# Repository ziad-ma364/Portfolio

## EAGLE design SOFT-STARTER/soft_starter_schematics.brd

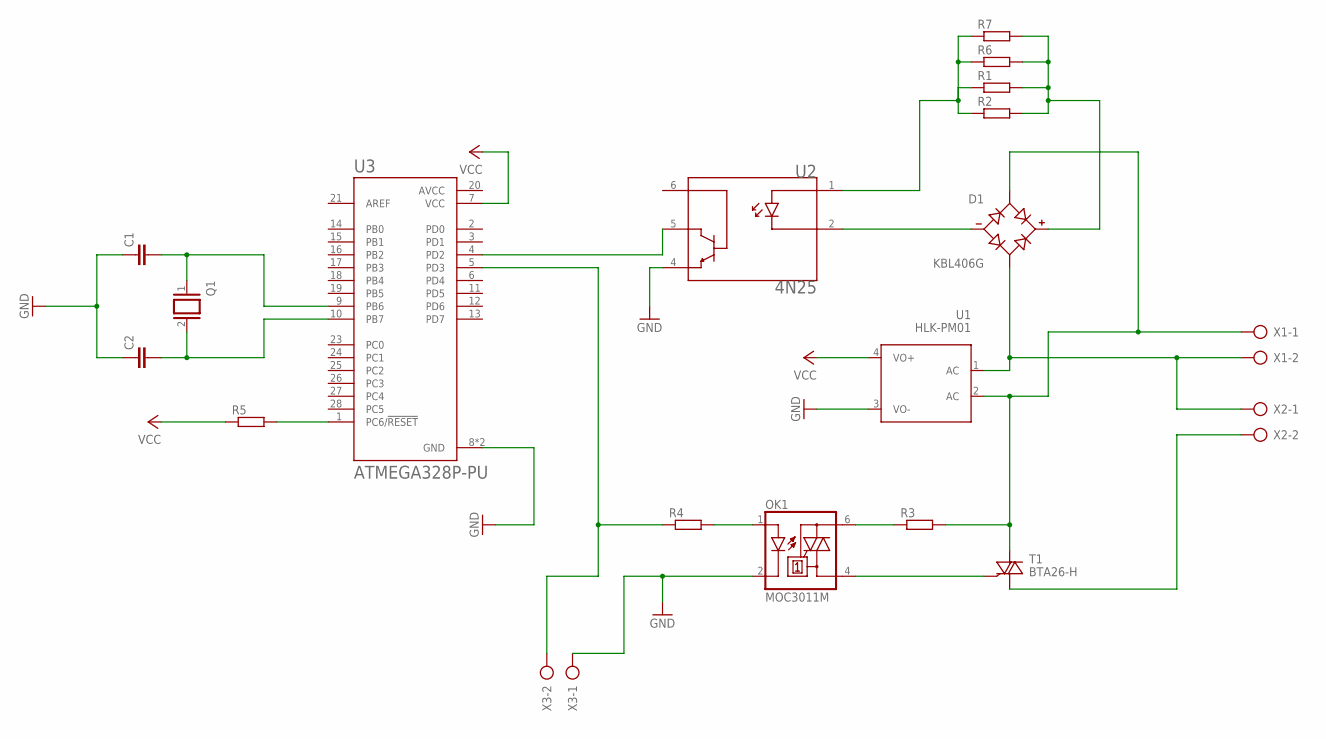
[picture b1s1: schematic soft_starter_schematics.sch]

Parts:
C1, C2: C2.5/2; C2.5-2
D1: KBL406G; SIP600W130P510L1900H1630Q4
OK1: MOC3011M; DIL06
Q1: XTAL/S; QS
R1, R2, R3, R4, R5, R6, R7: R-EU_0207/10; 0207/10
T1: BTA26-H; TOP3L-1
U1: HLK-PM01
U2: 4N25; DIP762W50P254L712H400Q6N
U3: ATMEGA328P-PU; DIP794W46P254L2967H457Q28B
X1, X2, X3: AK300/2

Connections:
AVCC: U3.20 (AVCC)
GND: C1.1, C2.1, OK1.2 (C), U1.3 (VO-), U2.4 (E), U3.8 (GND), U3.22 (GND), X3.1
unnamed: U2.5 (C), U3.4 (PD2)
unnamed: D1.-, U2.2 (K)
unnamed: D1.+, R1.2, R2.2, R6.2, R7.2
unnamed: R1.1, R2.1, R6.1, R7.1, U2.1 (A)
unnamed: D1.AC2, U1.1 (AC), X1.2, X2.1
unnamed: R4.1, U3.5 (PD3), X3.2
unnamed: T1.A1, X2.2
unnamed: OK1.4 (A1), T1.G
unnamed: OK1.6 (A2), R3.1
unnamed: R5.2, U3.1 (PC6/!RESET)
unnamed: OK1.1 (A), R4.2
unnamed: C2.2, Q1.2, U3.10 (PB7)
unnamed: C1.2, Q1.1, U3.9 (PB6)
unnamed: D1.AC1, R3.2, T1.A2, U1.2 (AC), X1.1
VCC: R5.1, U1.4 (VO+), U3.7 (VCC)

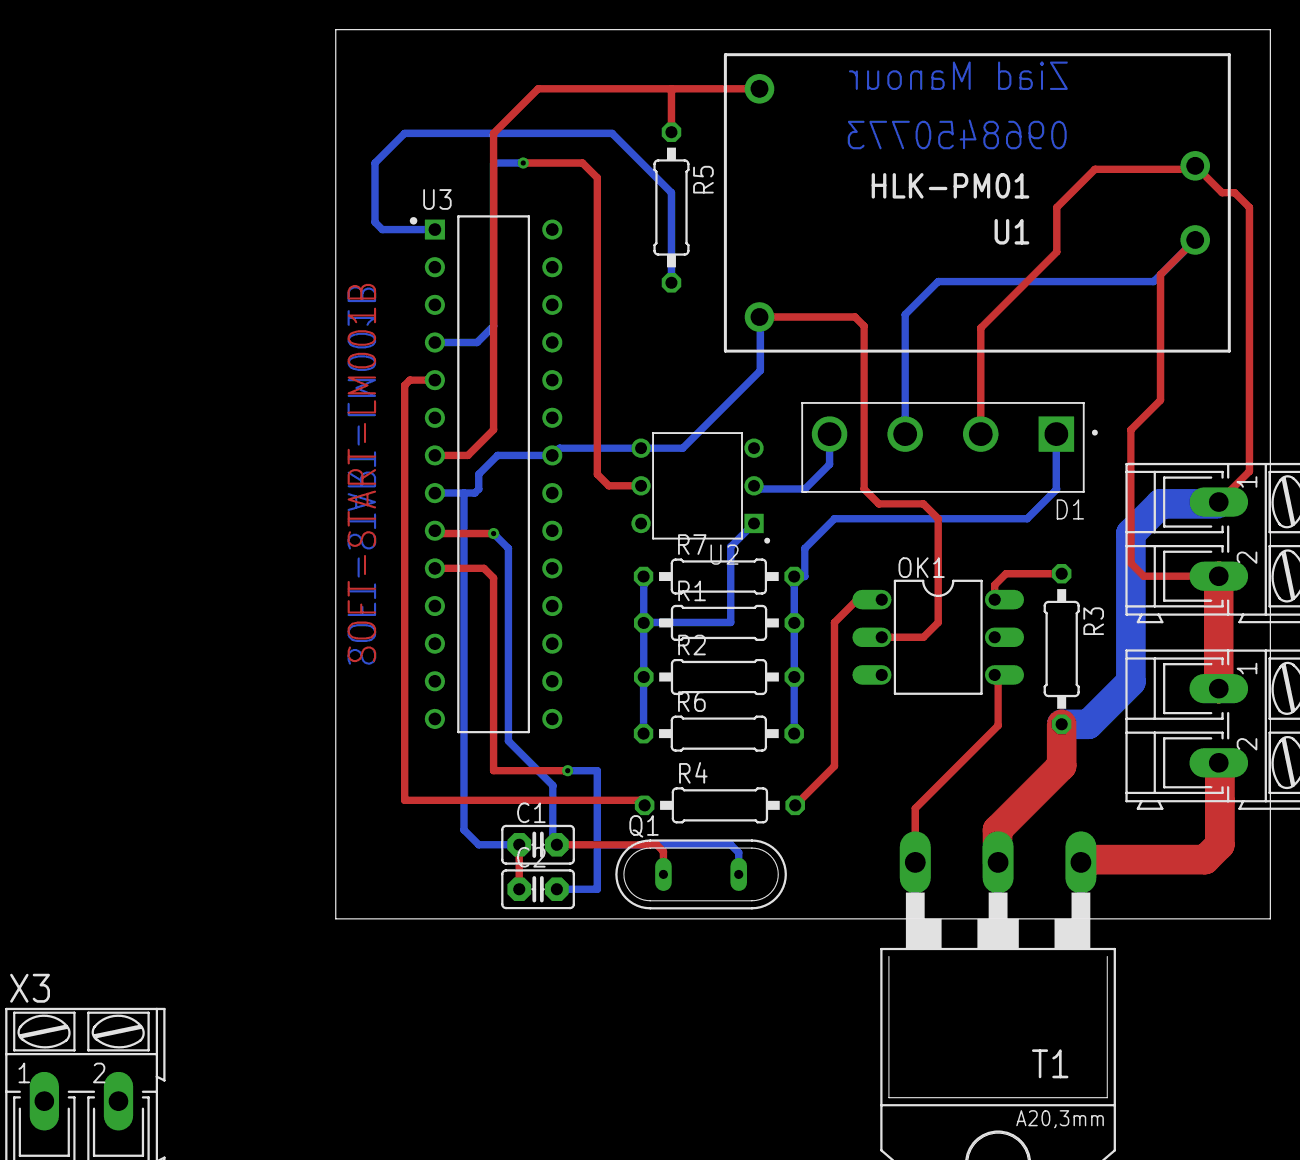
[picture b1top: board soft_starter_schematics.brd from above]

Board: 2 copper layers, 63.1 x 60.0 mm, 19 parts (0 on the bottom side), 16 nets.

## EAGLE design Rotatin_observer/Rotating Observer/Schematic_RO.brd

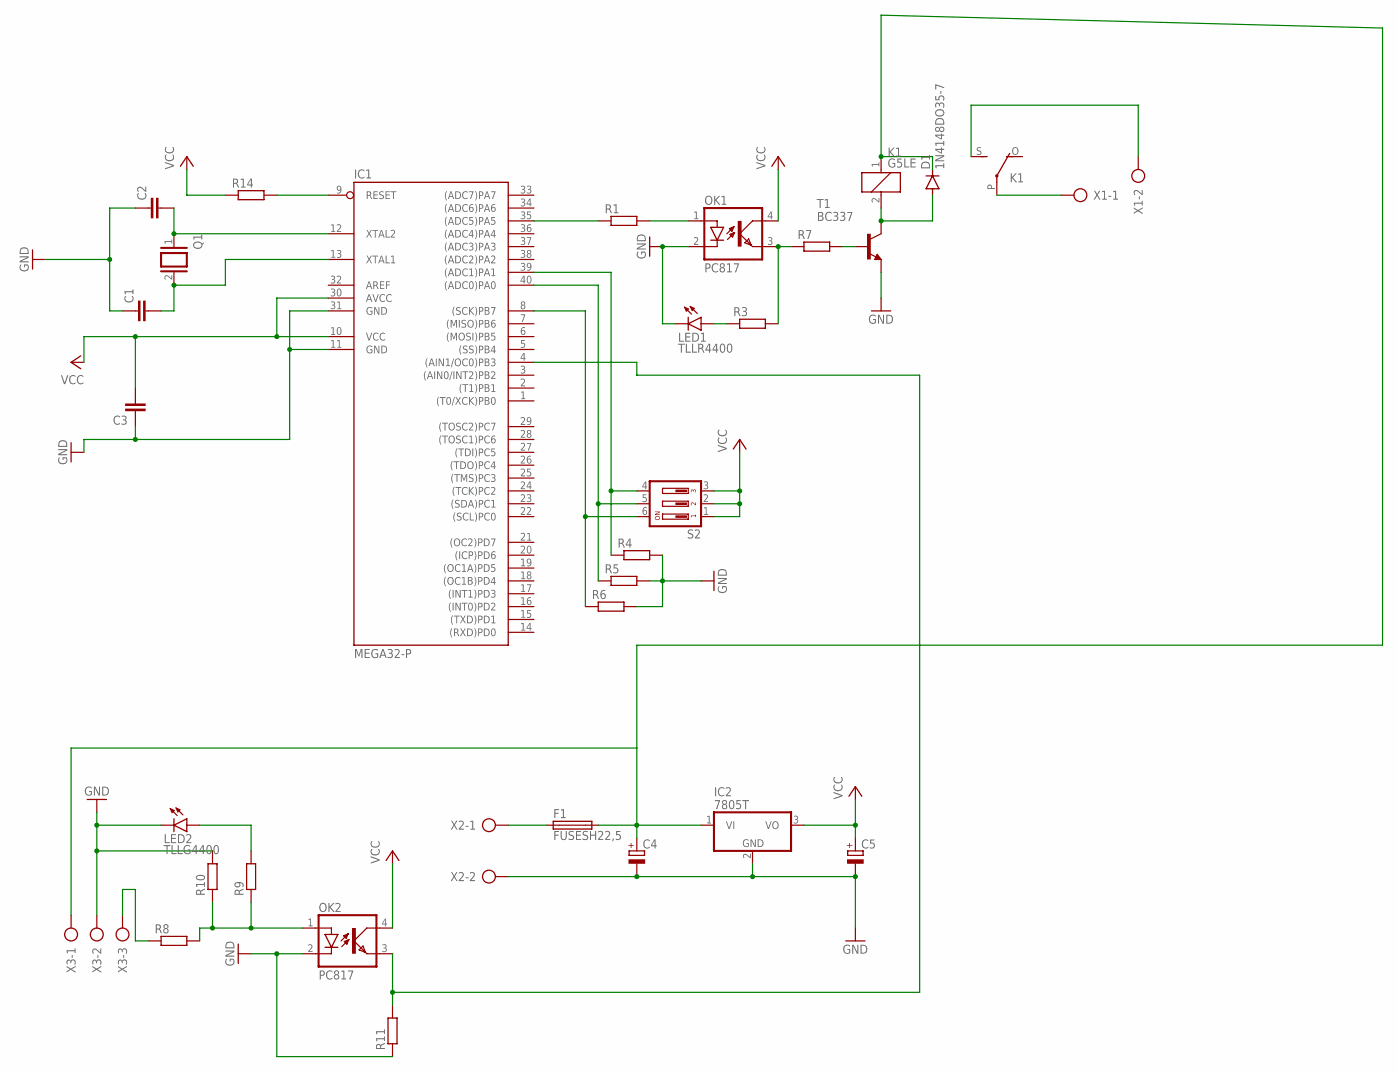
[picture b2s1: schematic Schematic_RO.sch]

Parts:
C1, C2, C3: C2,5-3; C2.5-3
C4, C5: CPOL-EUE2,5-6E; E2,5-6E
D1: 1N4148DO35-7; DO35-7
F1: FUSESH22,5; SH22,5
IC1: MEGA32-P; DIL40
IC2: 7805T; TO220H
K1: G5LE
LED1: TLLR4400; LED3MM
LED2: TLLG4400; LED3MM
OK1, OK2: PC817; DIL04
Q1: XTAL/S; QS
R1, R3, R4, R5, R6, R7, R8, R9, R10, R11, R14: R-EU_0204/7; 0204/7
S2: DIP03YL
T1: BC337; TO92
X1, X2: AK300/2
X3: AK300/3

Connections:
GND: C1.1, C2.1, C3.1, C4.-, C5.-, IC1.11 (GND), IC1.31 (GND), IC2.2 (GND), LED1.K (C), LED2.K (C), OK1.2 (C), OK2.2 (C), R4.2, R5.2, R6.2, R10.2, R11.1, T1.1 (E), X2.2, X3.2
unnamed: C2.2, IC1.12 (XTAL2), Q1.1
unnamed: C1.2, IC1.13 (XTAL1), Q1.2
unnamed: IC1.9 (RESET), R14.2
unnamed: IC1.39 ((ADC1)PA1), R4.1, S2.4
unnamed: IC1.40 ((ADC0)PA0), R5.1, S2.5
unnamed: IC1.8 ((SCK)PB7), R6.1, S2.6
unnamed: IC1.35 ((ADC5)PA5), R1.1
unnamed: OK1.1 (A), R1.2
unnamed: OK1.3 (EMIT), R3.2, R7.1
unnamed: R7.2, T1.2 (B)
unnamed: LED1.A, R3.1
unnamed: D1.A, K1.2, T1.3 (C)
unnamed: R8.1, X3.3
unnamed: K1.P, X1.1
unnamed: K1.S, X1.2
unnamed: F1.1, X2.1
unnamed: IC1.4 ((AIN1/OC0)PB3), OK2.3 (EMIT), R11.2
unnamed: C4.+, D1.C, F1.2, IC2.1 (VI), K1.1, X3.1
unnamed: OK2.1 (A), R8.2, R9.1, R10.1
unnamed: LED2.A, R9.2
VCC: C3.2, C5.+, IC1.10 (VCC), IC1.30 (AVCC), IC2.3 (VO), OK1.4 (COL), OK2.4 (COL), R14.1, S2.1, S2.2, S2.3

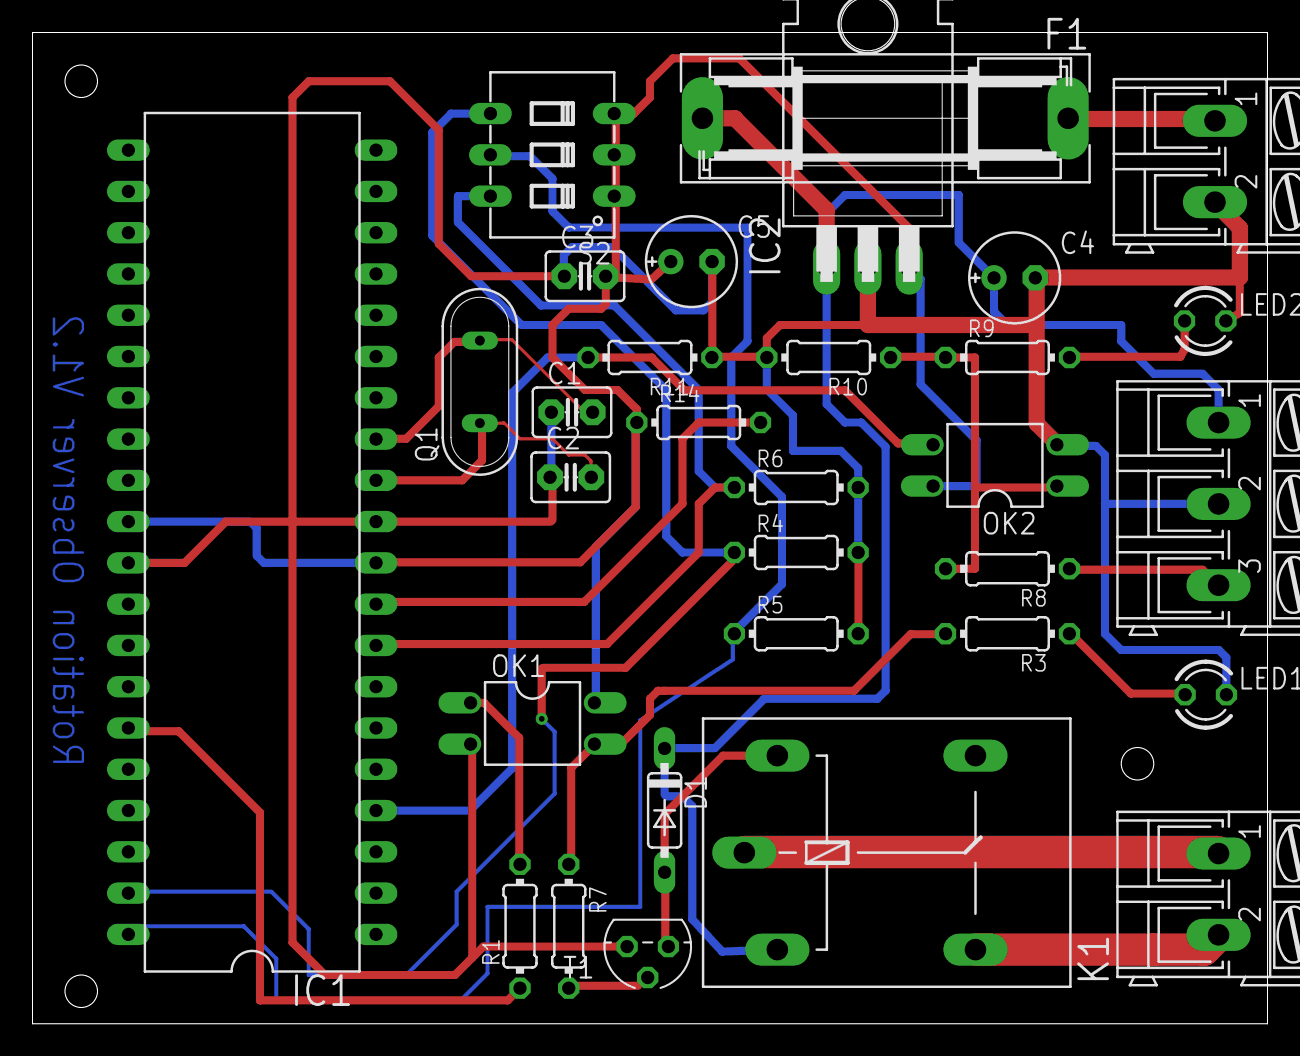
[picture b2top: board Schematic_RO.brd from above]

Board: 2 copper layers, 76.0 x 61.0 mm, 31 parts (0 on the bottom side), 22 nets.

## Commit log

2025-03-31 Create Graduation project
